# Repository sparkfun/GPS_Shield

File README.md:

SparkFun GPS Logger Shield
====================

[*SparkFun GPS Shield (GPS-13750)*](https://www.sparkfun.com/products/13750)

The [SparkFun GPS Logger Shield](https://www.sparkfun.com/products/13750) equips your Arduino with access to a GPS module, µSD memory card socket, and all of the other peripherals you'll need to turn your Arduino into a position-tracking, speed-monitoring, altitude-observing wonder logger. The shield is based around a [GP3906-TLP GPS Module](https://cdn.sparkfun.com/assets/learn_tutorials/4/6/8/GP3906-TLP_DataSheet_Rev_A01.pdf) -- a 66-channel GPS receiver featuring a MediaTek MT3339 architecture and an up to 10Hz update rate.

Repository Contents
-------------------

* **/Documentation** - Data sheets, additional product information 
* **/Firmware** - Example code 
* **/Hardware** - All Eagle design files (.brd, .sch)
* **/Production** - Production panel files (.brd)

Documentation
--------------
* **[Hookup Guide](https://learn.sparkfun.com/tutorials/gps-logger-shield-hookup-guide)** - Basic hookup guide for the SparkFun GPS Logger Shield.

Product Versions
----------------
* [GPS-13750](https://www.sparkfun.com/products/13750)- Initial release of the GPS Logger Shield

Version History
---------------
* [V_1.6](https://github.com/sparkfun/GPS_Shield/releases/tag/V_1.6) - Original GPS Shield - older GPS module, no µSD card support.

License Information
-------------------

This product is _**open source**_! 

Please review the LICENSE.md file for license information. 

If you have any questions or concerns on licensing, please contact techsupport@sparkfun.com.

Distributed as-is; no warranty is given.

- Your friends at SparkFun.

_<COLLABORATION CREDIT>_

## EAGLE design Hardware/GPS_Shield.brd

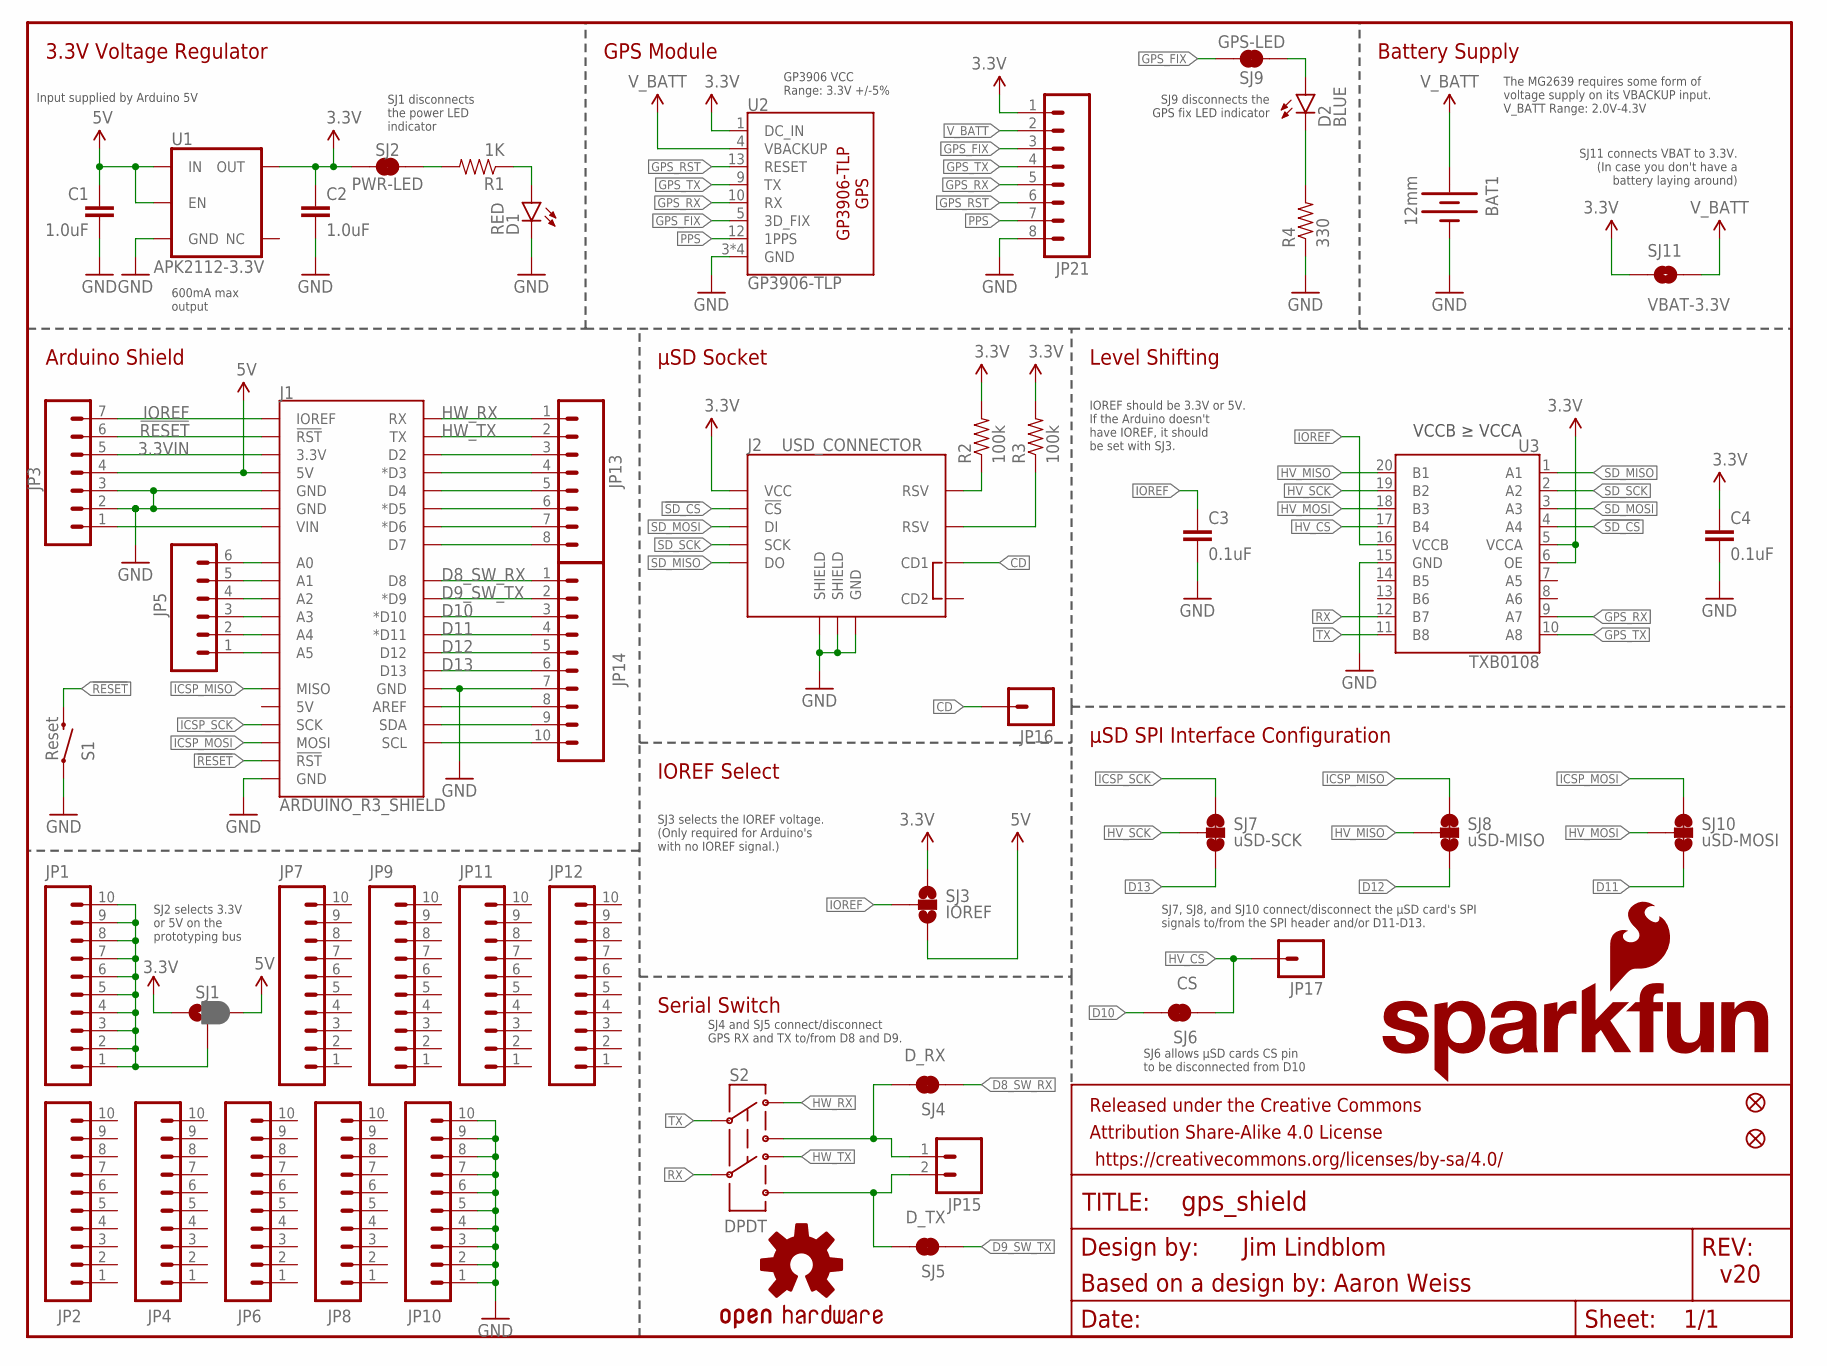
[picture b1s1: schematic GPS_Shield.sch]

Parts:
BAT1: 12mm; BATTCON_12MM
C1, C2: 1.0uF; 0603-CAP
C3, C4: 0.1uF; 0603-CAP
D1: RED; LED-0603
D2: BLUE; LED-0603
FRAME1: FRAME-LETTER; CREATIVE_COMMONS
J1: ARDUINO_R3_SHIELD; UNO_R3_SHIELD_ICSP_NOLABELS
J2: USD_CONNECTOR; MICRO-SD-SOCKET-PP
JP1, JP2, JP4, JP6, JP7, JP8, JP9, JP10, JP11, JP12, JP14: M10NO_SILK_PTH_FEMALE; 1X10_NO_SILK
JP3: M07NO_SILK; 1X07_NO_SILK
JP5: M06NO_SILK_FEMALE_PTH; 1X06_NO_SILK
JP13, JP21: M08NO_SILK_FEMALE_PTH; 1X08_NO_SILK
JP15: M021X02_NO_SILK; 1X02_NO_SILK
JP16, JP17: M01PTH_NO_SILK_YES_STOP; 1X01_NO_SILK
JP19, JP20: FIDUCIAL1X2; FIDUCIAL-1X2
LOGO1: OSHW-LOGOM; OSHW-LOGO-M
LOGO2: SFE_LOGO_NAME_FLAME.1_INCH; SFE_LOGO_NAME_FLAME_.1
R1: 1K; 0603-RES
R2, R3: 100k; 0603-RES
R4: 330; 0603-RES
S1: Reset; TACTILE-SWITCH-SMD
S2: DPDT; AYZ0202
SJ1: JUMPER-PAD-3-2OF3_NC_BY_PASTE; PAD-JUMPER-3-2OF3_NC_BY_PASTE_YES_SILK_FULL_BOX
SJ2: PWR-LED; PAD-JUMPER-2-NC_BY_TRACE_YES_SILK
SJ3: IOREF; PAD-JUMPER-3-NO_YES_SILK
SJ4: D_RX; PAD-JUMPER-2-NC_BY_TRACE_YES_SILK
SJ5: D_TX; PAD-JUMPER-2-NC_BY_TRACE_YES_SILK
SJ6: CS; PAD-JUMPER-2-NC_BY_TRACE_YES_SILK
SJ7: uSD-SCK; PAD-JUMPER-3-3OF3_NC_BY_TRACE_YES_SILK_FULL_BOX
SJ8: uSD-MISO; PAD-JUMPER-3-3OF3_NC_BY_TRACE_YES_SILK_FULL_BOX
SJ9: GPS-LED; PAD-JUMPER-2-NC_BY_TRACE_YES_SILK
SJ10: uSD-MOSI; PAD-JUMPER-3-3OF3_NC_BY_TRACE_YES_SILK_FULL_BOX
SJ11: VBAT-3.3V; PAD-JUMPER-2-NO_YES_SILK
U1: APK2112-3.3V; SOT23-5
U2: GP3906-TLP
U3: TXB0108; UFDFN-20

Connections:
3.3V: C2.1, C4.1, J2.VCC, JP21.1, R2.2, R3.2, SJ1.1, SJ2.1, SJ3.1, SJ11.1, U1.5 (OUT), U2.1 (DC_IN), U3.5 (VCCA), U3.6 (OE)
3.3VIN: J1.3.3V, JP3.5
5V: C1.1, J1.5V, JP3.4, SJ1.3, SJ3.3, U1.1 (IN), U1.3 (EN)
!RESET!: J1.RES (!RST!), J1.RST_ICSP (!RST!), JP3.6, S1.3 (2)
!SD_CS!: J2.CS (!CS), U3.4 (A4)
CD: J2.CD1, JP16.1
D8_SW_RX: J1.D8, JP14.1, SJ4.1
D9_SW_TX: J1.D9 (*D9), JP14.2, SJ5.1
D10: J1.D10 (*D10), JP14.3, SJ6.2
D11: J1.D11 (*D11), JP14.4, SJ10.3
D12: J1.D12, JP14.5, SJ8.3
D13: J1.D13, JP14.6, SJ7.3
GND: BAT1.GND (-), C1.2, C2.2, C3.2, C4.2, D1.C, J1.GND@0 (GND), J1.GND@1 (GND), J1.GND@2 (GND), J1.GND_ICSP (GND), J2.GND, J2.GND1 (SHIELD), J2.GND3 (SHIELD), JP3.2, JP3.3, JP10.1, JP10.2, JP10.3, JP10.4, JP10.5, JP10.6, JP10.7, JP10.8, JP10.9, JP10.10, JP14.7, JP21.8, R4.1, S1.1, U1.2 (GND), U2.3 (GND), U2.8 (GND), U2.11 (GND), U2.20 (GND), U3.15 (GND)
GPS_FIX: JP21.3, SJ9.2, U2.5 (3D_FIX)
GPS_RST: JP21.6, U2.13 (RESET)
GPS_RX: JP21.5, U2.10 (RX), U3.9 (A7)
GPS_TX: JP21.4, U2.9 (TX), U3.10 (A8)
HV_CS: JP17.1, SJ6.1, U3.17 (B4)
HV_MISO: SJ8.2, U3.20 (B1)
HV_MOSI: SJ10.2, U3.18 (B3)
HV_SCK: SJ7.2, U3.19 (B2)
HW_RX: J1.RX, JP13.1, S2.1
HW_TX: J1.TX, JP13.2, S2.4
ICSP_MISO: J1.MISO, SJ8.1
ICSP_MOSI: J1.MOSI, SJ10.1
ICSP_SCK: J1.SCK, SJ7.1
IOREF: C3.1, J1.IOREF, JP3.7, SJ3.2, U3.16 (VCCB)
unnamed: D1.A, R1.1
unnamed: D2.C, R4.2
unnamed: J1.A5, JP5.1
unnamed: J1.A4, JP5.2
unnamed: J1.D2, JP13.3
unnamed: J1.D3 (*D3), JP13.4
unnamed: J1.D4, JP13.5
unnamed: J1.D5 (*D5), JP13.6
unnamed: J1.D6 (*D6), JP13.7
unnamed: J1.D7, JP13.8
unnamed: J1.A3, JP5.3
unnamed: J1.A2, JP5.4
unnamed: J1.A1, JP5.5
unnamed: J1.A0, JP5.6
unnamed: R1.2, SJ2.2
unnamed: JP1.1, JP1.2, JP1.3, JP1.4, JP1.5, JP1.6, JP1.7, JP1.8, JP1.9, JP1.10, SJ1.2
unnamed: D2.A, SJ9.1
unnamed: J2.RSV1 (RSV), R2.1
unnamed: J2.RSV2 (RSV), R3.1
unnamed: J1.AREF, JP14.8
unnamed: J1.SDA, JP14.9
unnamed: J1.SCL, JP14.10
unnamed: J1.VIN, JP3.1
unnamed: JP15.2, S2.6, SJ5.2
unnamed: JP15.1, S2.3, SJ4.2
PPS: JP21.7, U2.12 (1PPS)
RX: S2.5, U3.12 (B7)
SD_MISO: J2.DO, U3.1 (A1)
SD_MOSI: J2.DI, U3.3 (A3)
SD_SCK: J2.SCLK (SCK), U3.2 (A2)
TX: S2.2, U3.11 (B8)
V_BATT: BAT1.PWR@1 (+), JP21.2, SJ11.2, U2.4 (VBACKUP)

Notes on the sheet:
GPS Module
Arduino Shield
Serial Switch
Jim Lindblom
v20
Based on a design by: Aaron Weiss
µSD Socket
Level Shifting
3.3V Voltage Regulator
µSD SPI Interface Configuration
IOREF Select
Input supplied by Arduino 5V
600mA max output
SJ1 disconnects the power LED indicator
SJ9 disconnects the GPS fix LED indicator
SJ2 selects 3.3V or 5V on the prototyping bus
VCCB ≥ VCCA
IOREF should be 3.3V or 5V. If the Arduino doesn't have IOREF, it should be set with SJ3.
SJ3 selects the IOREF voltage. (Only required for Arduino's with no IOREF signal.)
SJ7, SJ8, and SJ10 connect/disconnect the µSD card's SPI signals to/from the SPI header and/or D11-D13.
SJ6 allows µSD cards CS pin to be disconnected from D10
SJ4 and SJ5 connect/disconnect GPS RX and TX to/from D8 and D9.
GP3906 VCC Range: 3.3V +/-5%
SJ11 connects VBAT to 3.3V. (In case you don't have a battery laying around)
Battery Supply
The MG2639 requires some form of voltage supply on its VBACKUP input. V_BATT Range: 2.0V-4.3V

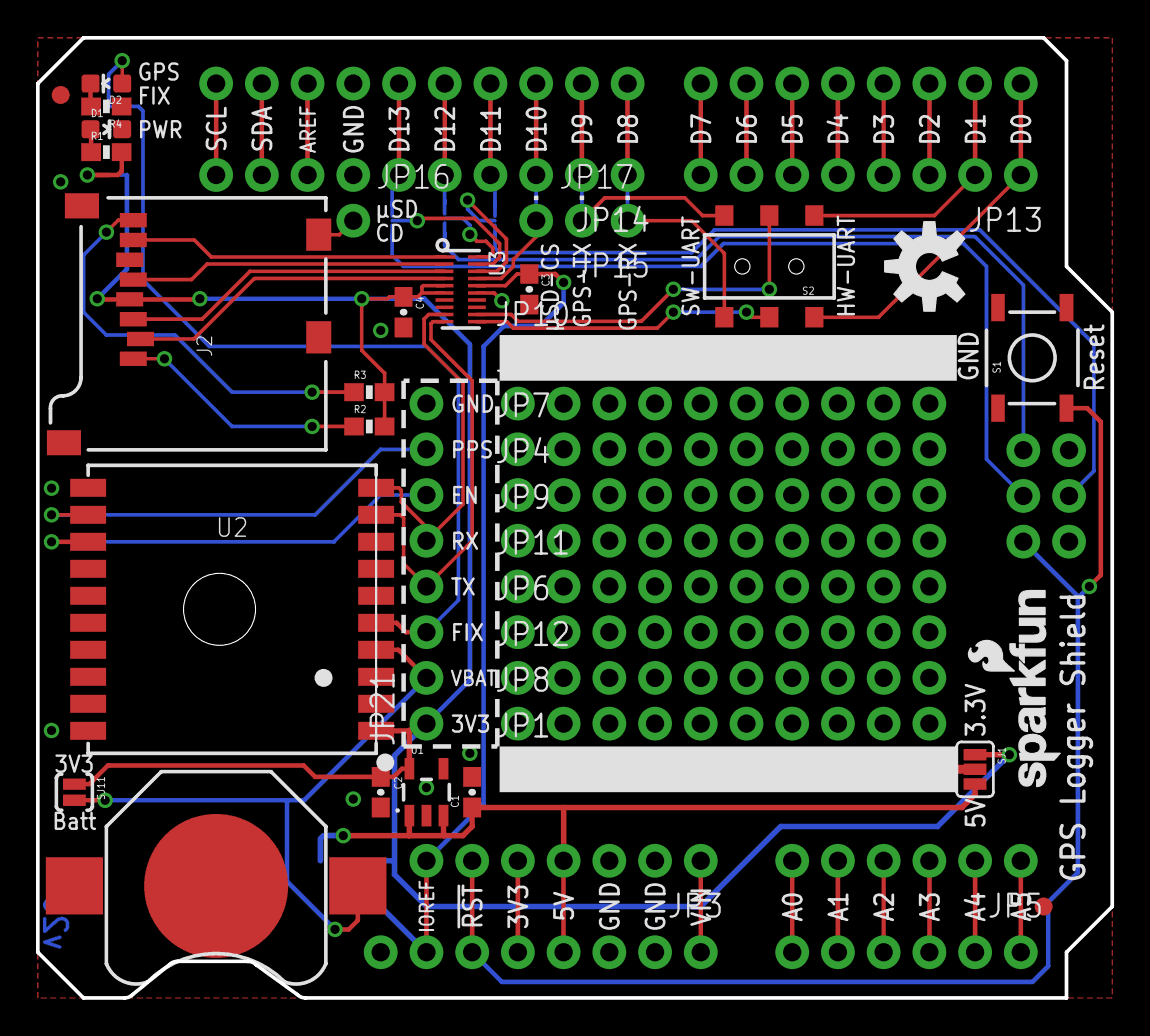
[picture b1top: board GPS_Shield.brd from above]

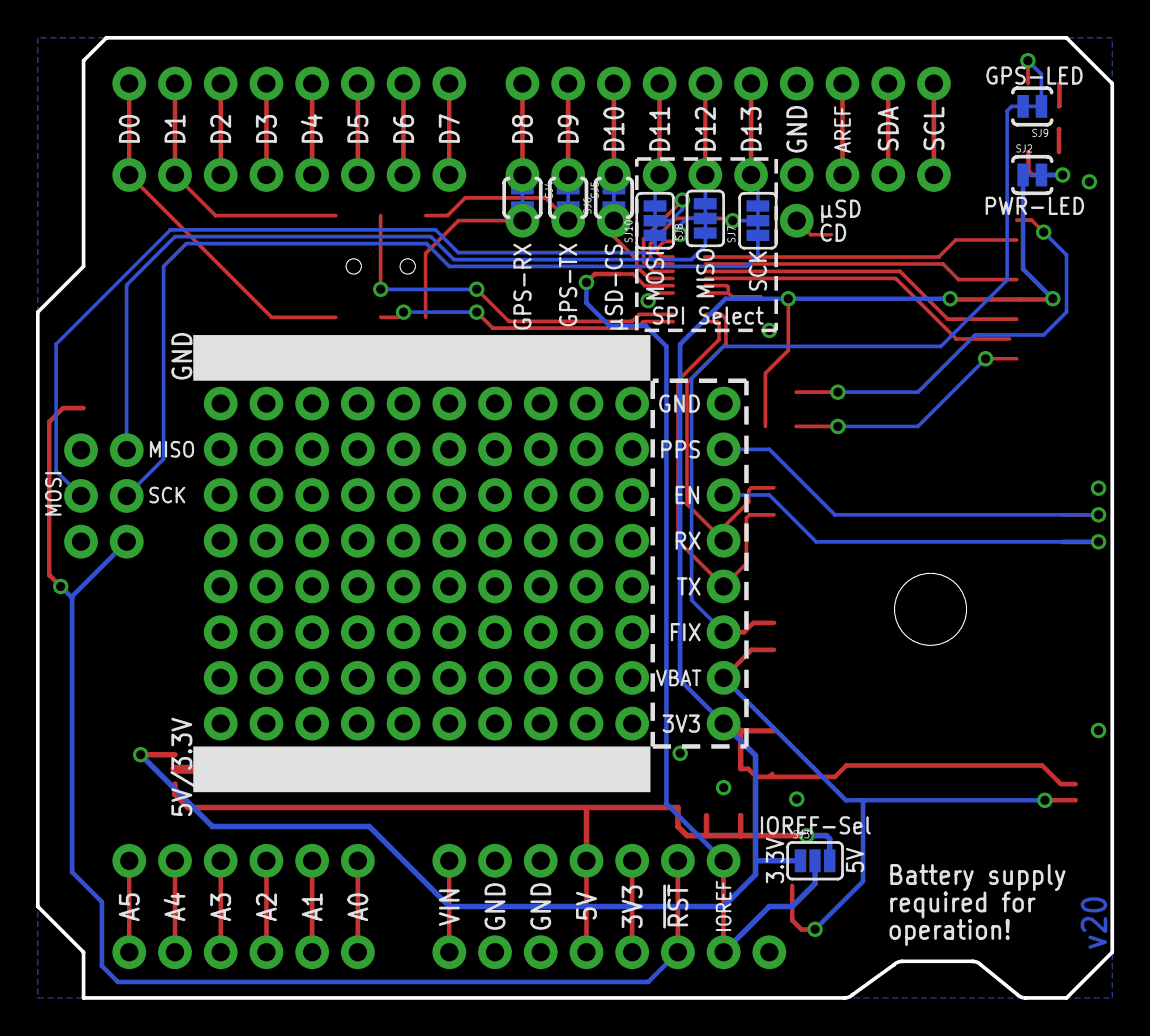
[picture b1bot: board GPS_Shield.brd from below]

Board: 2 copper layers, 59.7 x 53.3 mm, 52 parts (9 on the bottom side), 59 nets.

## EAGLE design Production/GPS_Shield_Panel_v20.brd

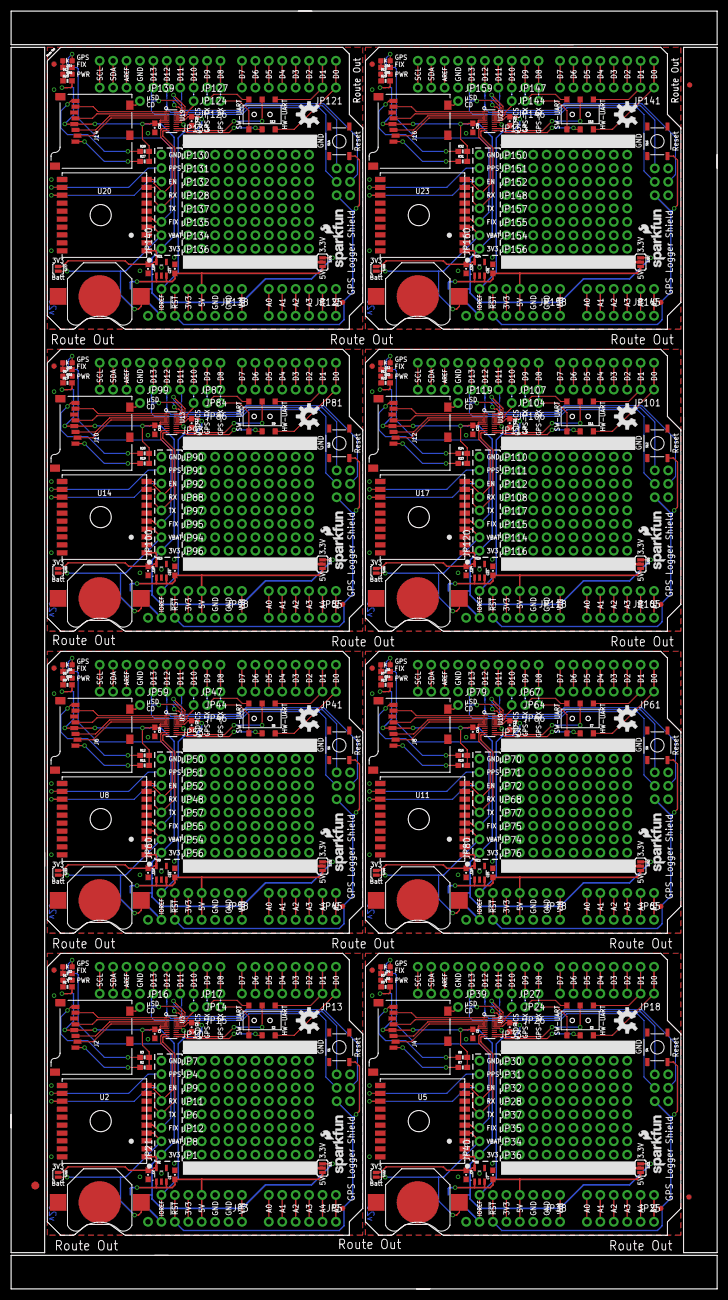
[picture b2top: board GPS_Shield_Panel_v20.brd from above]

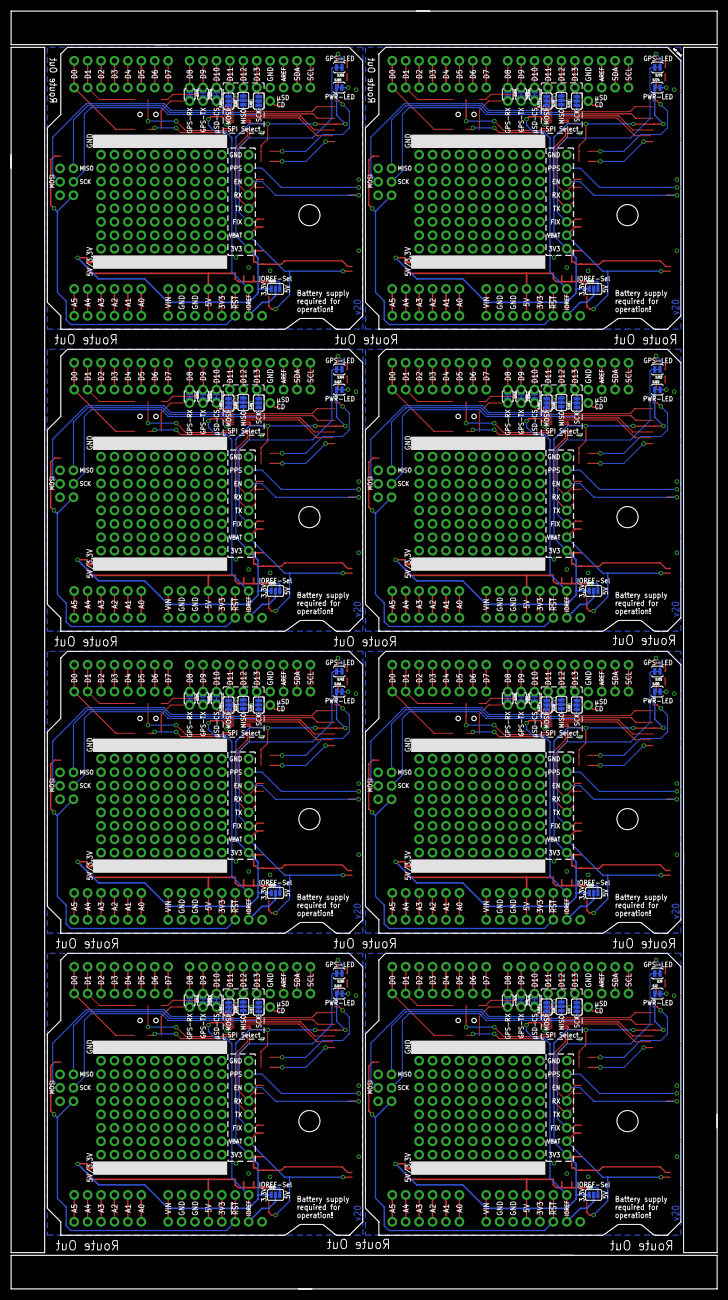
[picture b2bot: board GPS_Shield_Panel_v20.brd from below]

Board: 2 copper layers, 133.6 x 241.8 mm, 411 parts (72 on the bottom side), 472 nets.

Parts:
BAT1, BAT2, BAT3, BAT4, BAT5, BAT6, BAT7, BAT8: 12mm; BATTCON_12MM
C1, C2, C7, C8, C11, C12, C15, C16, C19, C20, C23, C24, C27, C28, C31, C32: 1.0uF; 0603-CAP
C3, C4, C5, C6, C9, C10, C13, C14, C17, C18, C21, C22, C25, C26, C29, C30: 0.1uF; 0603-CAP
D1, D3, D5, D7, D9, D11, D13, D15: RED; LED-0603
D2, D4, D6, D8, D10, D12, D14, D16: BLUE; LED-0603
E$1: FIDUCIAL-1.5X3
E$4, E$5: FIDUCIAL-1X2
J1, J3, J5, J7, J9, J11, J13, J15: ARDUINO_R3_SHIELD; UNO_R3_SHIELD_ICSP_NOLABELS
J2, J4, J6, J8, J10, J12, J14, J16: USD_CONNECTOR; MICRO-SD-SOCKET-PP
JP1, JP2, JP4, JP6, JP7, JP8, JP9, JP10, JP11, JP12, JP14, JP24, JP28, JP29, JP30, JP31, JP32, JP33, JP34, JP35, JP36, JP37, JP44, JP48, JP49, JP50, JP51, JP52, JP53, JP54, JP55, JP56, JP57, JP64, JP68, JP69, JP70, JP71, JP72, JP73, JP74, JP75, JP76, JP77, JP84, JP88, JP89, JP90, JP91, JP92, JP93, JP94, JP95, JP96, JP97, JP104, JP108, JP109, JP110, JP111, JP112, JP113, JP114, JP115, JP116, JP117, JP124, JP128, JP129, JP130, JP131, JP132, JP133, JP134, JP135, JP136, JP137, JP144, JP148, JP149, JP150, JP151, JP152, JP153, JP154, JP155, JP156, JP157: 1X10_NO_SILK
JP3, JP38, JP58, JP78, JP98, JP118, JP138, JP158: 1X07_NO_SILK
JP5, JP25, JP45, JP65, JP85, JP105, JP125, JP145: 1X06_NO_SILK
JP13, JP18, JP21, JP40, JP41, JP60, JP61, JP80, JP81, JP100, JP101, JP120, JP121, JP140, JP141, JP160: 1X08_NO_SILK
JP15, JP26, JP46, JP66, JP86, JP106, JP126, JP146: 1X02_NO_SILK
JP16, JP17, JP27, JP39, JP47, JP59, JP67, JP79, JP87, JP99, JP107, JP119, JP127, JP139, JP147, JP159: 1X01_NO_SILK
JP19, JP20, JP22, JP23, JP42, JP43, JP62, JP63, JP82, JP83, JP102, JP103, JP122, JP123, JP142, JP143: FIDUCIAL1X2; FIDUCIAL-1X2
LOGO1, LOGO4, LOGO6, LOGO8, LOGO10, LOGO12, LOGO14, LOGO16: OSHW-LOGOM; OSHW-LOGO-M
LOGO2, LOGO3, LOGO5, LOGO7, LOGO9, LOGO11, LOGO13, LOGO15: SFE_LOGO_NAME_FLAME.1_INCH; SFE_LOGO_NAME_FLAME_.1
R1, R5, R9, R13, R17, R21, R25, R29: 1K; 0603-RES
R2, R3, R7, R8, R11, R12, R15, R16, R19, R20, R23, R24, R27, R28, R31, R32: 100k; 0603-RES
R4, R6, R10, R14, R18, R22, R26, R30: 330; 0603-RES
S1, S4, S6, S8, S10, S12, S14, S16: Reset; TACTILE-SWITCH-SMD
S2, S3, S5, S7, S9, S11, S13, S15: DPDT; AYZ0202
SJ1, SJ21, SJ32, SJ43, SJ54, SJ65, SJ76, SJ87: PAD-JUMPER-3-2OF3_NC_BY_PASTE_YES_SILK_FULL_BOX
SJ2, SJ19, SJ30, SJ41, SJ52, SJ63, SJ74, SJ85: PWR-LED; PAD-JUMPER-2-NC_BY_TRACE_YES_SILK
SJ3, SJ14, SJ25, SJ36, SJ47, SJ58, SJ69, SJ80: IOREF; PAD-JUMPER-3-NO_YES_SILK
SJ4, SJ12, SJ23, SJ34, SJ45, SJ56, SJ67, SJ78: D_RX; PAD-JUMPER-2-NC_BY_TRACE_YES_SILK
SJ5, SJ13, SJ24, SJ35, SJ46, SJ57, SJ68, SJ79: D_TX; PAD-JUMPER-2-NC_BY_TRACE_YES_SILK
SJ6, SJ18, SJ29, SJ40, SJ51, SJ62, SJ73, SJ84: CS; PAD-JUMPER-2-NC_BY_TRACE_YES_SILK
SJ7, SJ17, SJ28, SJ39, SJ50, SJ61, SJ72, SJ83: uSD-SCK; PAD-JUMPER-3-3OF3_NC_BY_TRACE_YES_SILK_FULL_BOX
SJ8, SJ15, SJ26, SJ37, SJ48, SJ59, SJ70, SJ81: uSD-MISO; PAD-JUMPER-3-3OF3_NC_BY_TRACE_YES_SILK_FULL_BOX
SJ9, SJ20, SJ31, SJ42, SJ53, SJ64, SJ75, SJ86: GPS-LED; PAD-JUMPER-2-NC_BY_TRACE_YES_SILK
SJ10, SJ16, SJ27, SJ38, SJ49, SJ60, SJ71, SJ82: uSD-MOSI; PAD-JUMPER-3-3OF3_NC_BY_TRACE_YES_SILK_FULL_BOX
SJ11, SJ22, SJ33, SJ44, SJ55, SJ66, SJ77, SJ88: VBAT-3.3V; PAD-JUMPER-2-NO_YES_SILK
U1, U6, U9, U12, U15, U18, U21, U24: APK2112-3.3V; SOT23-5
U2, U5, U8, U11, U14, U17, U20, U23: GP3906-TLP
U3, U4, U7, U10, U13, U16, U19, U22: TXB0108; UFDFN-20

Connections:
3.3V: C2.1, C4.1, J2.VCC, JP21.1, R2.2, R3.2, SJ1.1, SJ2.1, SJ3.1, SJ11.1, U1.5, U2.1, U3.5, U3.6
3.3V1: C6.1, C8.1, J4.VCC, JP40.1, R7.2, R8.2, SJ14.1, SJ19.1, SJ21.1, SJ22.1, U4.5, U4.6, U5.1, U6.5
3.3V2: C10.1, C12.1, J6.VCC, JP60.1, R11.2, R12.2, SJ25.1, SJ30.1, SJ32.1, SJ33.1, U7.5, U7.6, U8.1, U9.5
3.3V3: C14.1, C16.1, J8.VCC, JP80.1, R15.2, R16.2, SJ36.1, SJ41.1, SJ43.1, SJ44.1, U10.5, U10.6, U11.1, U12.5
3.3V4: C18.1, C20.1, J10.VCC, JP100.1, R19.2, R20.2, SJ47.1, SJ52.1, SJ54.1, SJ55.1, U13.5, U13.6, U14.1, U15.5
3.3V5: C22.1, C24.1, J12.VCC, JP120.1, R23.2, R24.2, SJ58.1, SJ63.1, SJ65.1, SJ66.1, U16.5, U16.6, U17.1, U18.5
3.3V6: C26.1, C28.1, J14.VCC, JP140.1, R27.2, R28.2, SJ69.1, SJ74.1, SJ76.1, SJ77.1, U19.5, U19.6, U20.1, U21.5
3.3V7: C30.1, C32.1, J16.VCC, JP160.1, R31.2, R32.2, SJ80.1, SJ85.1, SJ87.1, SJ88.1, U22.5, U22.6, U23.1, U24.5
3.3VIN: J1.3.3V, JP3.5
3.3VIN1: J3.3.3V, JP38.5
3.3VIN2: J5.3.3V, JP58.5
3.3VIN3: J7.3.3V, JP78.5
3.3VIN4: J9.3.3V, JP98.5
3.3VIN5: J11.3.3V, JP118.5
3.3VIN6: J13.3.3V, JP138.5
3.3VIN7: J15.3.3V, JP158.5
5V: C1.1, J1.5V, JP3.4, SJ1.3, SJ3.3, U1.1, U1.3
5V1: C7.1, J3.5V, JP38.4, SJ14.3, SJ21.3, U6.1, U6.3
5V2: C11.1, J5.5V, JP58.4, SJ25.3, SJ32.3, U9.1, U9.3
5V3: C15.1, J7.5V, JP78.4, SJ36.3, SJ43.3, U12.1, U12.3
5V4: C19.1, J9.5V, JP98.4, SJ47.3, SJ54.3, U15.1, U15.3
5V5: C23.1, J11.5V, JP118.4, SJ58.3, SJ65.3, U18.1, U18.3
5V6: C27.1, J13.5V, JP138.4, SJ69.3, SJ76.3, U21.1, U21.3
5V7: C31.1, J15.5V, JP158.4, SJ80.3, SJ87.3, U24.1, U24.3
!RESET!: J1.RES, J1.RST_ICSP, JP3.6, S1.3
!RESET!1: J3.RES, J3.RST_ICSP, JP38.6, S4.3
!RESET!2: J5.RES, J5.RST_ICSP, JP58.6, S6.3
!RESET!3: J7.RES, J7.RST_ICSP, JP78.6, S8.3
!RESET!4: J9.RES, J9.RST_ICSP, JP98.6, S10.3
!RESET!5: J11.RES, J11.RST_ICSP, JP118.6, S12.3
!RESET!6: J13.RES, J13.RST_ICSP, JP138.6, S14.3
!RESET!7: J15.RES, J15.RST_ICSP, JP158.6, S16.3
!SD_CS!: J2.CS, U3.4
!SD_CS!1: J4.CS, U4.4
!SD_CS!2: J6.CS, U7.4
!SD_CS!3: J8.CS, U10.4
!SD_CS!4: J10.CS, U13.4
!SD_CS!5: J12.CS, U16.4
!SD_CS!6: J14.CS, U19.4
!SD_CS!7: J16.CS, U22.4
CD: J2.CD1, JP16.1
CD1: J4.CD1, JP39.1
CD2: J6.CD1, JP59.1
CD3: J8.CD1, JP79.1
CD4: J10.CD1, JP99.1
CD5: J12.CD1, JP119.1
CD6: J14.CD1, JP139.1
CD7: J16.CD1, JP159.1
D1: J3.D10, JP24.3, SJ18.2
D2: J3.D11, JP24.4, SJ16.3
D3: J3.D12, JP24.5, SJ15.3
D4: J3.D13, JP24.6, SJ17.3
D5: J5.D10, JP44.3, SJ29.2
D6: J5.D11, JP44.4, SJ27.3
D7: J5.D12, JP44.5, SJ26.3
D8: J5.D13, JP44.6, SJ28.3
D8_SW_RX: J1.D8, JP14.1, SJ4.1
D8_SW_RX1: J3.D8, JP24.1, SJ12.1
D8_SW_RX2: J5.D8, JP44.1, SJ23.1
D8_SW_RX3: J7.D8, JP64.1, SJ34.1
D8_SW_RX4: J9.D8, JP84.1, SJ45.1
D8_SW_RX5: J11.D8, JP104.1, SJ56.1
D8_SW_RX6: J13.D8, JP124.1, SJ67.1
D8_SW_RX7: J15.D8, JP144.1, SJ78.1
D9: J7.D10, JP64.3, SJ40.2
D9_SW_TX: J1.D9, JP14.2, SJ5.1
D9_SW_TX1: J3.D9, JP24.2, SJ13.1
D9_SW_TX2: J5.D9, JP44.2, SJ24.1
D9_SW_TX3: J7.D9, JP64.2, SJ35.1
D9_SW_TX4: J9.D9, JP84.2, SJ46.1
D9_SW_TX5: J11.D9, JP104.2, SJ57.1
D9_SW_TX6: J13.D9, JP124.2, SJ68.1
D9_SW_TX7: J15.D9, JP144.2, SJ79.1
D10: J1.D10, JP14.3, SJ6.2
D11: J1.D11, JP14.4, SJ10.3
D12: J1.D12, JP14.5, SJ8.3
D13: J1.D13, JP14.6, SJ7.3
D14: J7.D11, JP64.4, SJ38.3
D15: J7.D12, JP64.5, SJ37.3
D16: J7.D13, JP64.6, SJ39.3
D17: J9.D10, JP84.3, SJ51.2
D18: J9.D11, JP84.4, SJ49.3
D19: J9.D12, JP84.5, SJ48.3
D20: J9.D13, JP84.6, SJ50.3
D21: J11.D10, JP104.3, SJ62.2
D22: J11.D11, JP104.4, SJ60.3
D23: J11.D12, JP104.5, SJ59.3
D24: J11.D13, JP104.6, SJ61.3
D25: J13.D10, JP124.3, SJ73.2
D26: J13.D11, JP124.4, SJ71.3
D27: J13.D12, JP124.5, SJ70.3
D28: J13.D13, JP124.6, SJ72.3
D29: J15.D10, JP144.3, SJ84.2
D30: J15.D11, JP144.4, SJ82.3
D31: J15.D12, JP144.5, SJ81.3
D32: J15.D13, JP144.6, SJ83.3
GND: BAT1.GND, C1.2, C2.2, C3.2, C4.2, D1.C, J1.GND@0, J1.GND@1, J1.GND@2, J1.GND_ICSP, J2.GND, J2.GND1, J2.GND3, JP3.2, JP3.3, JP10.1, JP10.2, JP10.3, JP10.4, JP10.5, JP10.6, JP10.7, JP10.8, JP10.9, JP10.10, JP14.7, JP21.8, R4.1, S1.1, U1.2, U2.3, U2.8, U2.11, U2.20, U3.15
GND1: BAT2.GND, C5.2, C6.2, C7.2, C8.2, D3.C, J3.GND@0, J3.GND@1, J3.GND@2, J3.GND_ICSP, J4.GND, J4.GND1, J4.GND3, JP24.7, JP33.1, JP33.2, JP33.3, JP33.4, JP33.5, JP33.6, JP33.7, JP33.8, JP33.9, JP33.10, JP38.2, JP38.3, JP40.8, R6.1, S4.1, U4.15, U5.3, U5.8, U5.11, U5.20, U6.2
GND2: BAT3.GND, C9.2, C10.2, C11.2, C12.2, D5.C, J5.GND@0, J5.GND@1, J5.GND@2, J5.GND_ICSP, J6.GND, J6.GND1, J6.GND3, JP44.7, JP53.1, JP53.2, JP53.3, JP53.4, JP53.5, JP53.6, JP53.7, JP53.8, JP53.9, JP53.10, JP58.2, JP58.3, JP60.8, R10.1, S6.1, U7.15, U8.3, U8.8, U8.11, U8.20, U9.2
GND3: BAT4.GND, C13.2, C14.2, C15.2, C16.2, D7.C, J7.GND@0, J7.GND@1, J7.GND@2, J7.GND_ICSP, J8.GND, J8.GND1, J8.GND3, JP64.7, JP73.1, JP73.2, JP73.3, JP73.4, JP73.5, JP73.6, JP73.7, JP73.8, JP73.9, JP73.10, JP78.2, JP78.3, JP80.8, R14.1, S8.1, U10.15, U11.3, U11.8, U11.11, U11.20, U12.2
GND4: BAT5.GND, C17.2, C18.2, C19.2, C20.2, D9.C, J9.GND@0, J9.GND@1, J9.GND@2, J9.GND_ICSP, J10.GND, J10.GND1, J10.GND3, JP84.7, JP93.1, JP93.2, JP93.3, JP93.4, JP93.5, JP93.6, JP93.7, JP93.8, JP93.9, JP93.10, JP98.2, JP98.3, JP100.8, R18.1, S10.1, U13.15, U14.3, U14.8, U14.11, U14.20, U15.2
GND5: BAT6.GND, C21.2, C22.2, C23.2, C24.2, D11.C, J11.GND@0, J11.GND@1, J11.GND@2, J11.GND_ICSP, J12.GND, J12.GND1, J12.GND3, JP104.7, JP113.1, JP113.2, JP113.3, JP113.4, JP113.5, JP113.6, JP113.7, JP113.8, JP113.9, JP113.10, JP118.2, JP118.3, JP120.8, R22.1, S12.1, U16.15, U17.3, U17.8, U17.11, U17.20, U18.2
GND6: BAT7.GND, C25.2, C26.2, C27.2, C28.2, D13.C, J13.GND@0, J13.GND@1, J13.GND@2, J13.GND_ICSP, J14.GND, J14.GND1, J14.GND3, JP124.7, JP133.1, JP133.2, JP133.3, JP133.4, JP133.5, JP133.6, JP133.7, JP133.8, JP133.9, JP133.10, JP138.2, JP138.3, JP140.8, R26.1, S14.1, U19.15, U20.3, U20.8, U20.11, U20.20, U21.2
GND7: BAT8.GND, C29.2, C30.2, C31.2, C32.2, D15.C, J15.GND@0, J15.GND@1, J15.GND@2, J15.GND_ICSP, J16.GND, J16.GND1, J16.GND3, JP144.7, JP153.1, JP153.2, JP153.3, JP153.4, JP153.5, JP153.6, JP153.7, JP153.8, JP153.9, JP153.10, JP158.2, JP158.3, JP160.8, R30.1, S16.1, U22.15, U23.3, U23.8, U23.11, U23.20, U24.2
GPS_FIX: JP21.3, SJ9.2, U2.5
GPS_FIX1: JP40.3, SJ20.2, U5.5
GPS_FIX2: JP60.3, SJ31.2, U8.5
GPS_FIX3: JP80.3, SJ42.2, U11.5
GPS_FIX4: JP100.3, SJ53.2, U14.5
GPS_FIX5: JP120.3, SJ64.2, U17.5
GPS_FIX6: JP140.3, SJ75.2, U20.5
GPS_FIX7: JP160.3, SJ86.2, U23.5
GPS_RST: JP21.6, U2.13
GPS_RST1: JP40.6, U5.13
GPS_RST2: JP60.6, U8.13
GPS_RST3: JP80.6, U11.13
GPS_RST4: JP100.6, U14.13
GPS_RST5: JP120.6, U17.13
GPS_RST6: JP140.6, U20.13
GPS_RST7: JP160.6, U23.13
GPS_RX: JP21.5, U2.10, U3.9
GPS_RX1: JP40.5, U4.9, U5.10
GPS_RX2: JP60.5, U7.9, U8.10
GPS_RX3: JP80.5, U10.9, U11.10
GPS_RX4: JP100.5, U13.9, U14.10
GPS_RX5: JP120.5, U16.9, U17.10
GPS_RX6: JP140.5, U19.9, U20.10
GPS_RX7: JP160.5, U22.9, U23.10
GPS_TX: JP21.4, U2.9, U3.10
GPS_TX1: JP40.4, U4.10, U5.9
GPS_TX2: JP60.4, U7.10, U8.9
GPS_TX3: JP80.4, U10.10, U11.9
GPS_TX4: JP100.4, U13.10, U14.9
GPS_TX5: JP120.4, U16.10, U17.9
GPS_TX6: JP140.4, U19.10, U20.9
GPS_TX7: JP160.4, U22.10, U23.9
HV_CS: JP17.1, SJ6.1, U3.17
HV_CS1: JP27.1, SJ18.1, U4.17
HV_CS2: JP47.1, SJ29.1, U7.17
HV_CS3: JP67.1, SJ40.1, U10.17
HV_CS4: JP87.1, SJ51.1, U13.17
HV_CS5: JP107.1, SJ62.1, U16.17
HV_CS6: JP127.1, SJ73.1, U19.17
HV_CS7: JP147.1, SJ84.1, U22.17
HV_MISO: SJ8.2, U3.20
HV_MISO1: SJ15.2, U4.20
HV_MISO2: SJ26.2, U7.20
HV_MISO3: SJ37.2, U10.20
HV_MISO4: SJ48.2, U13.20
HV_MISO5: SJ59.2, U16.20
HV_MISO6: SJ70.2, U19.20
HV_MISO7: SJ81.2, U22.20
HV_MOSI: SJ10.2, U3.18
HV_MOSI1: SJ16.2, U4.18
HV_MOSI2: SJ27.2, U7.18
HV_MOSI3: SJ38.2, U10.18
HV_MOSI4: SJ49.2, U13.18
HV_MOSI5: SJ60.2, U16.18
HV_MOSI6: SJ71.2, U19.18
HV_MOSI7: SJ82.2, U22.18
HV_SCK: SJ7.2, U3.19
HV_SCK1: SJ17.2, U4.19
HV_SCK2: SJ28.2, U7.19
HV_SCK3: SJ39.2, U10.19
HV_SCK4: SJ50.2, U13.19
HV_SCK5: SJ61.2, U16.19
HV_SCK6: SJ72.2, U19.19
HV_SCK7: SJ83.2, U22.19
HW_RX: J1.RX, JP13.1, S2.1
HW_RX1: J3.RX, JP18.1, S3.1
HW_RX2: J5.RX, JP41.1, S5.1
HW_RX3: J7.RX, JP61.1, S7.1
HW_RX4: J9.RX, JP81.1, S9.1
HW_RX5: J11.RX, JP101.1, S11.1
HW_RX6: J13.RX, JP121.1, S13.1
HW_RX7: J15.RX, JP141.1, S15.1
HW_TX: J1.TX, JP13.2, S2.4
HW_TX1: J3.TX, JP18.2, S3.4
HW_TX2: J5.TX, JP41.2, S5.4
HW_TX3: J7.TX, JP61.2, S7.4
HW_TX4: J9.TX, JP81.2, S9.4
HW_TX5: J11.TX, JP101.2, S11.4
HW_TX6: J13.TX, JP121.2, S13.4
HW_TX7: J15.TX, JP141.2, S15.4
ICSP_MISO: J1.MISO, SJ8.1
ICSP_MISO1: J3.MISO, SJ15.1
ICSP_MISO2: J5.MISO, SJ26.1
ICSP_MISO3: J7.MISO, SJ37.1
ICSP_MISO4: J9.MISO, SJ48.1
ICSP_MISO5: J11.MISO, SJ59.1
ICSP_MISO6: J13.MISO, SJ70.1
ICSP_MISO7: J15.MISO, SJ81.1
ICSP_MOSI: J1.MOSI, SJ10.1
ICSP_MOSI1: J3.MOSI, SJ16.1
ICSP_MOSI2: J5.MOSI, SJ27.1
ICSP_MOSI3: J7.MOSI, SJ38.1
ICSP_MOSI4: J9.MOSI, SJ49.1
ICSP_MOSI5: J11.MOSI, SJ60.1
ICSP_MOSI6: J13.MOSI, SJ71.1
ICSP_MOSI7: J15.MOSI, SJ82.1
ICSP_SCK: J1.SCK, SJ7.1
ICSP_SCK1: J3.SCK, SJ17.1
ICSP_SCK2: J5.SCK, SJ28.1
ICSP_SCK3: J7.SCK, SJ39.1
ICSP_SCK4: J9.SCK, SJ50.1
ICSP_SCK5: J11.SCK, SJ61.1
ICSP_SCK6: J13.SCK, SJ72.1
ICSP_SCK7: J15.SCK, SJ83.1
IOREF: C3.1, J1.IOREF, JP3.7, SJ3.2, U3.16
IOREF1: C5.1, J3.IOREF, JP38.7, SJ14.2, U4.16
IOREF2: C9.1, J5.IOREF, JP58.7, SJ25.2, U7.16
IOREF3: C13.1, J7.IOREF, JP78.7, SJ36.2, U10.16
IOREF4: C17.1, J9.IOREF, JP98.7, SJ47.2, U13.16
IOREF5: C21.1, J11.IOREF, JP118.7, SJ58.2, U16.16
IOREF6: C25.1, J13.IOREF, JP138.7, SJ69.2, U19.16
IOREF7: C29.1, J15.IOREF, JP158.7, SJ80.2, U22.16
unnamed: D1.A, R1.1
unnamed: D2.C, R4.2
unnamed: J1.A5, JP5.1
unnamed: J1.A4, JP5.2
unnamed: J1.D2, JP13.3
unnamed: J1.D3, JP13.4
unnamed: J1.D4, JP13.5
unnamed: J1.D5, JP13.6
unnamed: J1.D6, JP13.7
unnamed: J1.D7, JP13.8
unnamed: J1.A3, JP5.3
unnamed: J1.A2, JP5.4
unnamed: J1.A1, JP5.5
unnamed: J1.A0, JP5.6
unnamed: R1.2, SJ2.2
unnamed: JP1.1, JP1.2, JP1.3, JP1.4, JP1.5, JP1.6, JP1.7, JP1.8, JP1.9, JP1.10, SJ1.2
unnamed: D2.A, SJ9.1
unnamed: J2.RSV1, R2.1
unnamed: J2.RSV2, R3.1
unnamed: J1.AREF, JP14.8
unnamed: J1.SDA, JP14.9
unnamed: J1.SCL, JP14.10
unnamed: D3.A, R5.1
unnamed: J1.VIN, JP3.1
unnamed: JP26.2, S3.6, SJ13.2
unnamed: JP26.1, S3.3, SJ12.2
unnamed: J3.D2, JP18.3
unnamed: J3.D3, JP18.4
unnamed: J3.D4, JP18.5
unnamed: J3.D5, JP18.6
unnamed: J3.D6, JP18.7
unnamed: J3.D7, JP18.8
unnamed: J3.AREF, JP24.8
unnamed: J3.SDA, JP24.9
unnamed: J3.SCL, JP24.10
unnamed: J3.VIN, JP38.1
unnamed: J3.A5, JP25.1
unnamed: J3.A4, JP25.2
unnamed: J3.A3, JP25.3
unnamed: J3.A2, JP25.4
unnamed: J3.A1, JP25.5
unnamed: J3.A0, JP25.6
unnamed: R5.2, SJ19.2
unnamed: D4.C, R6.2
unnamed: D4.A, SJ20.1
unnamed: JP36.1, JP36.2, JP36.3, JP36.4, JP36.5, JP36.6, JP36.7, JP36.8, JP36.9, JP36.10, SJ21.2
unnamed: J4.RSV1, R7.1
unnamed: J4.RSV2, R8.1
unnamed: D5.A, R9.1
unnamed: JP46.2, S5.6, SJ24.2
unnamed: JP46.1, S5.3, SJ23.2
unnamed: J5.D2, JP41.3
unnamed: J5.D3, JP41.4
unnamed: J5.D4, JP41.5
unnamed: J5.D5, JP41.6
unnamed: J5.D6, JP41.7
unnamed: J5.D7, JP41.8
unnamed: J5.AREF, JP44.8
unnamed: J5.SDA, JP44.9
unnamed: J5.SCL, JP44.10
unnamed: J5.VIN, JP58.1
unnamed: J5.A5, JP45.1
unnamed: J5.A4, JP45.2
unnamed: J5.A3, JP45.3
unnamed: J5.A2, JP45.4
unnamed: J5.A1, JP45.5
unnamed: J5.A0, JP45.6
unnamed: R9.2, SJ30.2
unnamed: D6.C, R10.2
unnamed: D6.A, SJ31.1
unnamed: JP56.1, JP56.2, JP56.3, JP56.4, JP56.5, JP56.6, JP56.7, JP56.8, JP56.9, JP56.10, SJ32.2
unnamed: J6.RSV1, R11.1
unnamed: J6.RSV2, R12.1
unnamed: D7.A, R13.1
unnamed: JP66.2, S7.6, SJ35.2
unnamed: JP66.1, S7.3, SJ34.2
unnamed: J7.D2, JP61.3
unnamed: J7.D3, JP61.4
unnamed: J7.D4, JP61.5
unnamed: J7.D5, JP61.6
unnamed: J7.D6, JP61.7
unnamed: J7.D7, JP61.8
unnamed: J7.AREF, JP64.8
unnamed: J7.SDA, JP64.9
unnamed: J7.SCL, JP64.10
unnamed: J7.VIN, JP78.1
unnamed: J7.A5, JP65.1
unnamed: J7.A4, JP65.2
unnamed: J7.A3, JP65.3
unnamed: J7.A2, JP65.4
unnamed: J7.A1, JP65.5
unnamed: J7.A0, JP65.6
unnamed: R13.2, SJ41.2
unnamed: D8.C, R14.2
unnamed: D8.A, SJ42.1
unnamed: JP76.1, JP76.2, JP76.3, JP76.4, JP76.5, JP76.6, JP76.7, JP76.8, JP76.9, JP76.10, SJ43.2
unnamed: J8.RSV1, R15.1
unnamed: J8.RSV2, R16.1
unnamed: D9.A, R17.1
unnamed: JP86.2, S9.6, SJ46.2
unnamed: JP86.1, S9.3, SJ45.2
unnamed: J9.D2, JP81.3
unnamed: J9.D3, JP81.4
unnamed: J9.D4, JP81.5
unnamed: J9.D5, JP81.6
unnamed: J9.D6, JP81.7
unnamed: J9.D7, JP81.8
unnamed: J9.AREF, JP84.8
unnamed: J9.SDA, JP84.9
unnamed: J9.SCL, JP84.10
unnamed: J9.VIN, JP98.1
unnamed: J9.A5, JP85.1
unnamed: J9.A4, JP85.2
unnamed: J9.A3, JP85.3
unnamed: J9.A2, JP85.4
unnamed: J9.A1, JP85.5
unnamed: J9.A0, JP85.6
unnamed: R17.2, SJ52.2
unnamed: D10.C, R18.2
unnamed: D10.A, SJ53.1
unnamed: JP15.2, S2.6, SJ5.2
unnamed: JP15.1, S2.3, SJ4.2
unnamed: JP96.1, JP96.2, JP96.3, JP96.4, JP96.5, JP96.6, JP96.7, JP96.8, JP96.9, JP96.10, SJ54.2
unnamed: J10.RSV1, R19.1
unnamed: J10.RSV2, R20.1
unnamed: D11.A, R21.1
unnamed: JP106.2, S11.6, SJ57.2
unnamed: JP106.1, S11.3, SJ56.2
unnamed: J11.D2, JP101.3
unnamed: J11.D3, JP101.4
unnamed: J11.D4, JP101.5
unnamed: J11.D5, JP101.6
unnamed: J11.D6, JP101.7
unnamed: J11.D7, JP101.8
unnamed: J11.AREF, JP104.8
unnamed: J11.SDA, JP104.9
unnamed: J11.SCL, JP104.10
unnamed: J11.VIN, JP118.1
unnamed: J11.A5, JP105.1
unnamed: J11.A4, JP105.2
unnamed: J11.A3, JP105.3
unnamed: J11.A2, JP105.4
unnamed: J11.A1, JP105.5
unnamed: J11.A0, JP105.6
unnamed: R21.2, SJ63.2
unnamed: D12.C, R22.2
unnamed: D12.A, SJ64.1
unnamed: JP116.1, JP116.2, JP116.3, JP116.4, JP116.5, JP116.6, JP116.7, JP116.8, JP116.9, JP116.10, SJ65.2
unnamed: J12.RSV1, R23.1
unnamed: J12.RSV2, R24.1
unnamed: D13.A, R25.1
unnamed: JP126.2, S13.6, SJ68.2
unnamed: JP126.1, S13.3, SJ67.2
unnamed: J13.D2, JP121.3
unnamed: J13.D3, JP121.4
unnamed: J13.D4, JP121.5
unnamed: J13.D5, JP121.6
unnamed: J13.D6, JP121.7
unnamed: J13.D7, JP121.8
unnamed: J13.AREF, JP124.8
unnamed: J13.SDA, JP124.9
unnamed: J13.SCL, JP124.10
unnamed: J13.VIN, JP138.1
unnamed: J13.A5, JP125.1
unnamed: J13.A4, JP125.2
unnamed: J13.A3, JP125.3
unnamed: J13.A2, JP125.4
unnamed: J13.A1, JP125.5
unnamed: J13.A0, JP125.6
unnamed: R25.2, SJ74.2
unnamed: D14.C, R26.2
unnamed: D14.A, SJ75.1
unnamed: JP136.1, JP136.2, JP136.3, JP136.4, JP136.5, JP136.6, JP136.7, JP136.8, JP136.9, JP136.10, SJ76.2
unnamed: J14.RSV1, R27.1
unnamed: J14.RSV2, R28.1
unnamed: D15.A, R29.1
unnamed: JP146.2, S15.6, SJ79.2
unnamed: JP146.1, S15.3, SJ78.2
unnamed: J15.D2, JP141.3
unnamed: J15.D3, JP141.4
unnamed: J15.D4, JP141.5
unnamed: J15.D5, JP141.6
unnamed: J15.D6, JP141.7
unnamed: J15.D7, JP141.8
unnamed: J15.AREF, JP144.8
unnamed: J15.SDA, JP144.9
unnamed: J15.SCL, JP144.10
unnamed: J15.VIN, JP158.1
unnamed: J15.A5, JP145.1
unnamed: J15.A4, JP145.2
unnamed: J15.A3, JP145.3
unnamed: J15.A2, JP145.4
unnamed: J15.A1, JP145.5
unnamed: J15.A0, JP145.6
unnamed: R29.2, SJ85.2
unnamed: D16.C, R30.2
unnamed: D16.A, SJ86.1
unnamed: JP156.1, JP156.2, JP156.3, JP156.4, JP156.5, JP156.6, JP156.7, JP156.8, JP156.9, JP156.10, SJ87.2
unnamed: J16.RSV1, R31.1
unnamed: J16.RSV2, R32.1
PPS: JP21.7, U2.12
PPS1: JP40.7, U5.12
PPS2: JP60.7, U8.12
PPS3: JP80.7, U11.12
PPS4: JP100.7, U14.12
PPS5: JP120.7, U17.12
PPS6: JP140.7, U20.12
PPS7: JP160.7, U23.12
RX: S2.5, U3.12
RX1: S3.5, U4.12
RX2: S5.5, U7.12
RX3: S7.5, U10.12
RX4: S9.5, U13.12
RX5: S11.5, U16.12
RX6: S13.5, U19.12
RX7: S15.5, U22.12
SD_MISO: J2.DO, U3.1
SD_MISO1: J4.DO, U4.1
SD_MISO2: J6.DO, U7.1
SD_MISO3: J8.DO, U10.1
SD_MISO4: J10.DO, U13.1
SD_MISO5: J12.DO, U16.1
SD_MISO6: J14.DO, U19.1
SD_MISO7: J16.DO, U22.1
SD_MOSI: J2.DI, U3.3
SD_MOSI1: J4.DI, U4.3
SD_MOSI2: J6.DI, U7.3
SD_MOSI3: J8.DI, U10.3
SD_MOSI4: J10.DI, U13.3
SD_MOSI5: J12.DI, U16.3
SD_MOSI6: J14.DI, U19.3
SD_MOSI7: J16.DI, U22.3
SD_SCK: J2.SCLK, U3.2
SD_SCK1: J4.SCLK, U4.2
SD_SCK2: J6.SCLK, U7.2
SD_SCK3: J8.SCLK, U10.2
SD_SCK4: J10.SCLK, U13.2
SD_SCK5: J12.SCLK, U16.2
SD_SCK6: J14.SCLK, U19.2
SD_SCK7: J16.SCLK, U22.2
TX: S2.2, U3.11
TX1: S3.2, U4.11
TX2: S5.2, U7.11
TX3: S7.2, U10.11
TX4: S9.2, U13.11
TX5: S11.2, U16.11
TX6: S13.2, U19.11
TX7: S15.2, U22.11
V_BATT: BAT1.PWR@1, JP21.2, SJ11.2, U2.4
V_BATT1: BAT2.PWR@1, JP40.2, SJ22.2, U5.4
V_BATT2: BAT3.PWR@1, JP60.2, SJ33.2, U8.4
V_BATT3: BAT4.PWR@1, JP80.2, SJ44.2, U11.4
V_BATT4: BAT5.PWR@1, JP100.2, SJ55.2, U14.4
V_BATT5: BAT6.PWR@1, JP120.2, SJ66.2, U17.4
V_BATT6: BAT7.PWR@1, JP140.2, SJ77.2, U20.4
V_BATT7: BAT8.PWR@1, JP160.2, SJ88.2, U23.4

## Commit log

2015-02-03 Initial commit with brd/sch
2015-03-11 Updating README, adding .git* files
2015-10-07 Initial commit of v2.0
    - Added micro SD socket
    - Switched GPS to new PCB-mountable version
    - Updated shield to R3 footprint
2015-10-12 Adding GPS module datasheet, ignoring backup lbr files
2015-10-12 Adding measures, cleaning up schematic
2015-10-12 Changing GP-735 module's VCC to 3.3V
2015-10-12 Moving GP-735 connector to bottom side, marking DNP
2015-10-14 Upping isolate to 0.01", adding some GND vias.
2015-10-14 Clarifying GPS's pin 1 indicator.
2015-11-16 Adding VBATT-to-3.3V jumper, breaking out VBATT.
2015-11-16 Changing DRU to SparkFun-2-Layer-Tight, slightly moving traces to accomodate.
2015-11-23 Schematic and trace cleanup.
2015-11-24 Removing GP-735 fp. Default 3.3/VBat jumper closed.
2015-11-24 Schematic cleanup
2015-11-24 Silkscreen adjustments.
2015-11-24 Upping paste on GPS module pins by 50%
2015-11-24 Default SJ11 to open.
2015-11-24 Adding note about battery required.
2015-11-30 Updating 12mm battery PROD_ID
2015-12-02 created panel v20
2016-02-09 Adding example code.
2016-02-11 Updating readme, adding license.

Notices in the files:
parts and their libraries:
SparkFun-Aesthetics: Licensing: Creative Commons ShareAlike 4.0 International - https://creativecommons.org/licenses/by-sa/4.0
SparkFun-Aesthetics: Released under the Creative Commons Attribution Share-Alike 4.0 License
SparkFun-Aesthetics: https://creativecommons.org/licenses/by-sa/4.0
